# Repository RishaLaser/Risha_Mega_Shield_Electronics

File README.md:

Risha_Mega_Shield_Electronics
=============================

Eagle Schematic and Board Files

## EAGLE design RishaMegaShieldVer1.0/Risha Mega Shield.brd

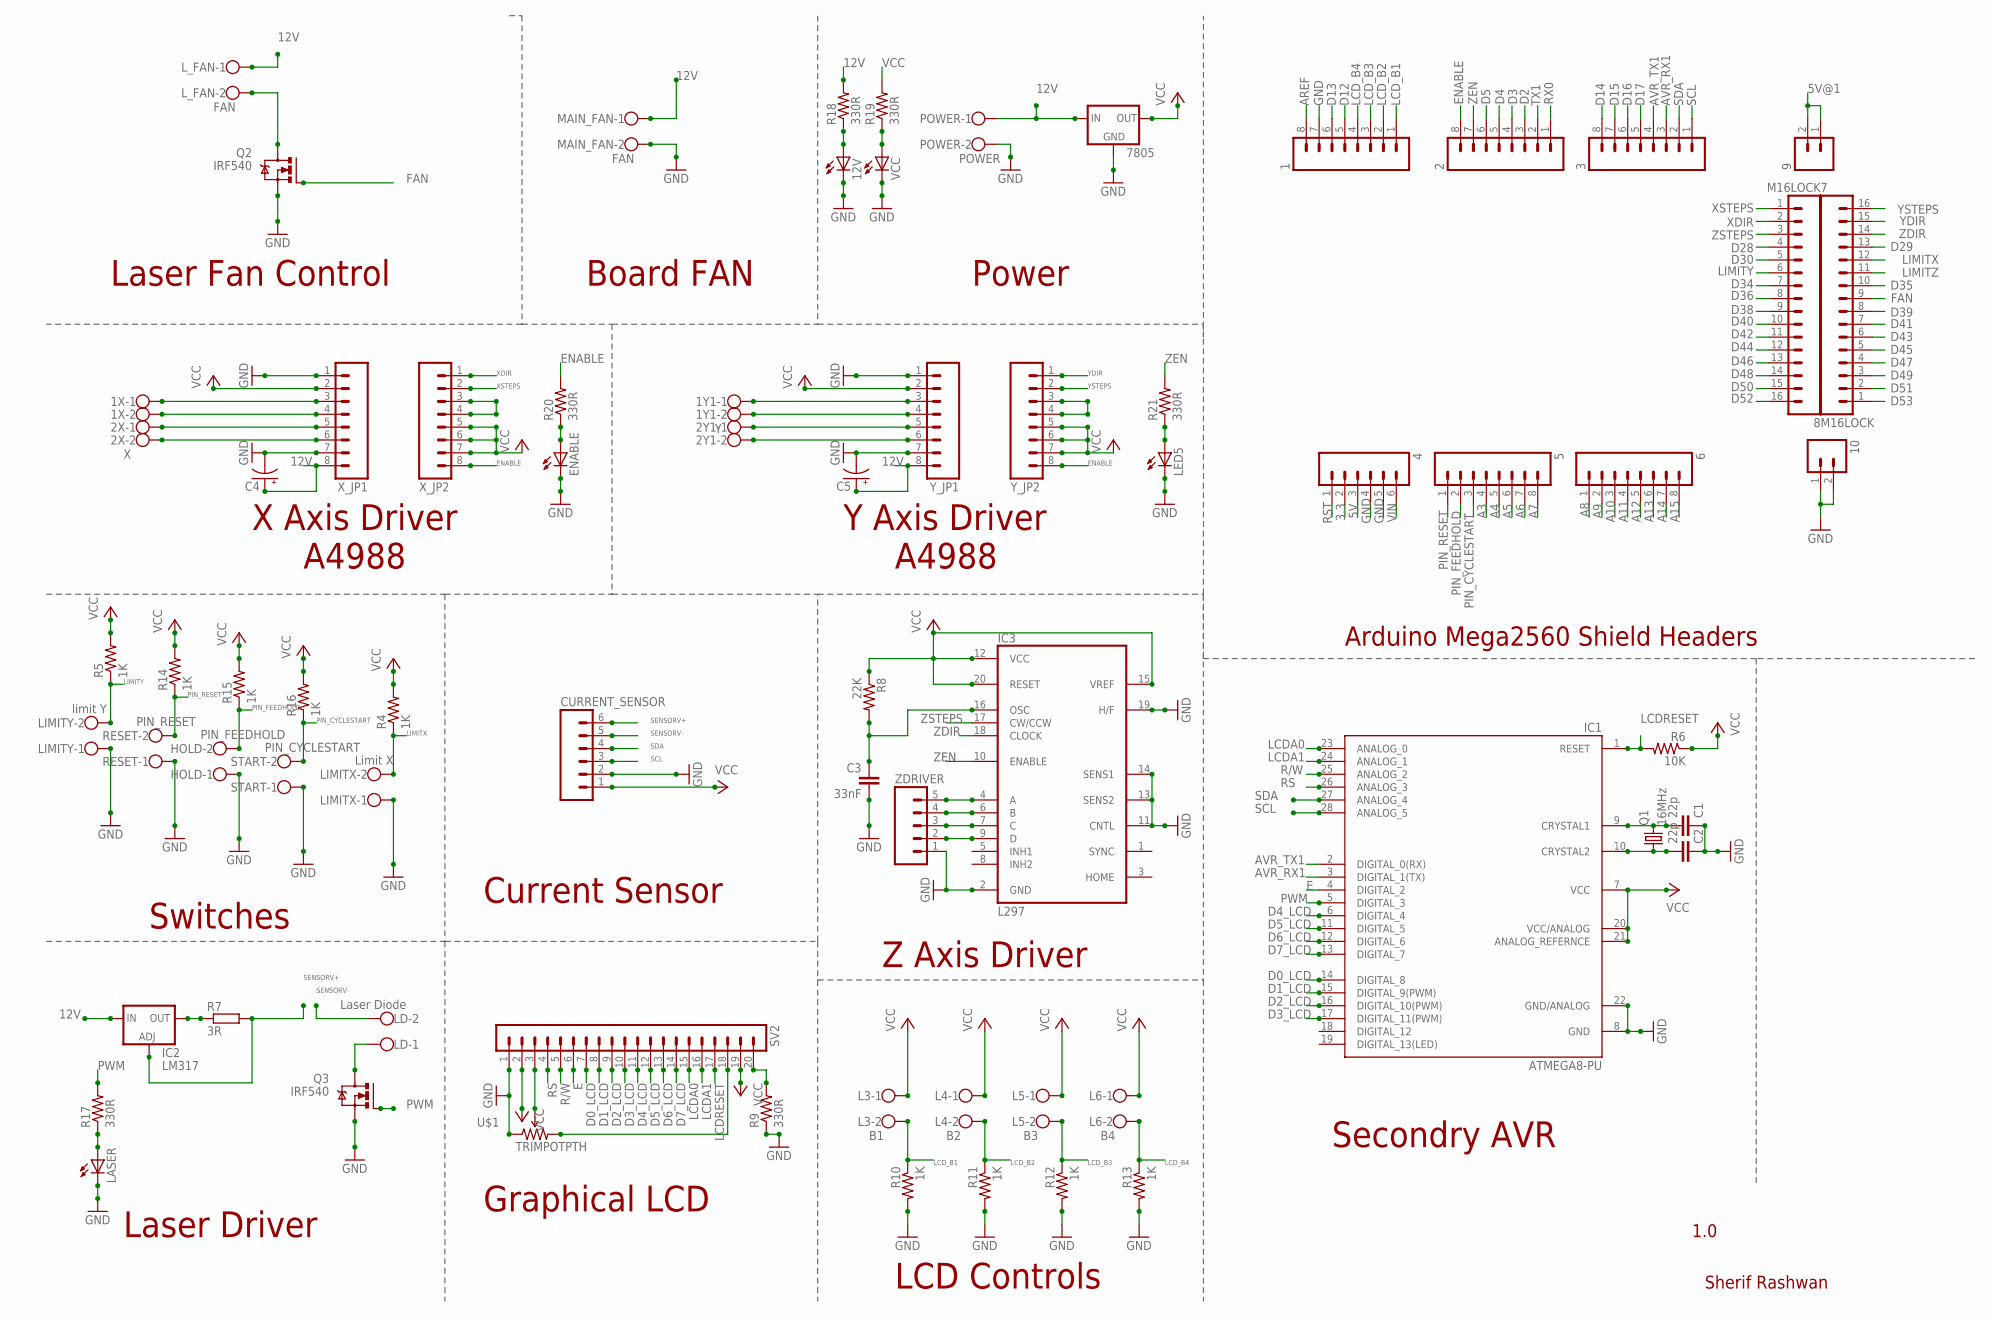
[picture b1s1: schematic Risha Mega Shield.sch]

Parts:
1, 2, 3, 5, 6: M08LOCK; 1X08_LOCK
1X, 2Y1: W237-102
1Y1: Y; W237-102
2X: X; W237-102
4: M06LOCK; 1X06_LOCK
7, 8: M16LOCK; 1X16_LOCK
9, 10: M02LOCK; 1X02_LOCK
12V: LED3MM
7805: V_REG_78XXSINK; TO220-IGO
C1, C2: 22p; C2.5-2
C3: 33nF; C2.5-2
C4, C5: CAP_POLPTH2; CPOL-RADIAL-10UF-25V
CURRENT_SENSOR: M06LONGPADS; 1X06_LONGPADS
ENABLE: LED3MM
HOLD: PIN_FEEDHOLD; W237-102
IC1: ATMEGA8-PU; DIL28-3
IC2: LM317; TO3-K02
IC3: L297; DIL20
L3: B1; W237-102
L4: B2; W237-102
L5: B3; W237-102
L6: B4; W237-102
LASER: LED3MM
LD: Laser Diode; W237-102
LED5: LED3MM
LIMITX: Limit X; W237-102
LIMITY: limit Y; W237-102
L_FAN: FAN; W237-102
MAIN_FAN: FAN; W237-102
POWER: POWER; W237-102
Q1: 16MHz; HC49US
Q2, Q3: IRF540; TO220BV
R4, R5, R10, R11, R12, R13, R14, R15, R16: 1K; 1/6W-RES
R6: 10K; 1/6W-RES
R7: 3R; 0309/12
R8: 22K; 1/6W-RES
R9, R17, R18, R19, R20, R21: 330R; 1/6W-RES
RESET: PIN_RESET; W237-102
START: PIN_CYCLESTART; W237-102
SV2: MA20-1W
U$1: TRIMPOTPTH; TRIM_POT_PTH
VCC: LED3MM
X_JP1, X_JP2: M08; 1X08
Y_JP1, Y_JP2: M08; 1X08
ZDRIVER: M05PTH_LONGPADS; 1X05_LONGPADS

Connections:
3.3: 4.2
5V: 4.3
5V@1: 9.1, 9.2
12V: 7805.IN, C4.1 (+), C5.1 (+), IC2.1 (IN), L_FAN.1, MAIN_FAN.1, POWER.1, R18.2, X_JP1.8, Y_JP1.8
A3: 5.4
A4: 5.5
A5: 5.6
A6: 5.7
A7: 5.8
A8: 6.1
A9: 6.2
A10: 6.3
A11: 6.4
A12: 6.5
A13: 6.6
A14: 6.7
A15: 6.8
AREF: 1.8
AVR_RX1: 3.3, IC1.3 (DIGITAL_1(TX))
AVR_TX1: 3.4, IC1.2 (DIGITAL_0(RX))
D0_LCD: IC1.14 (DIGITAL_8), SV2.7
D1_LCD: IC1.15 (DIGITAL_9(PWM)), SV2.8
D2: 2.3
D2_LCD: IC1.16 (DIGITAL_10(PWM)), SV2.9
D3: 2.4
D3_LCD: IC1.17 (DIGITAL_11(PWM)), SV2.10
D4: 2.5
D4_LCD: IC1.6 (DIGITAL_4), SV2.11
D5: 2.6
D5_LCD: IC1.11 (DIGITAL_5), SV2.12
D6_LCD: IC1.12 (DIGITAL_6), SV2.13
D7_LCD: IC1.13 (DIGITAL_7), SV2.14
D12: 1.5
D13: 1.6
D14: 3.8
D15: 3.7
D16: 3.6
D17: 3.5
D28: 8.4
D29: 7.13
D30: 8.5
D34: 8.7
D35: 7.10
D36: 8.8
D38: 8.9
D39: 7.8
D40: 8.10
D41: 7.7
D42: 8.11
D43: 7.6
D44: 8.12
D45: 7.5
D46: 8.13
D47: 7.4
D48: 8.14
D49: 7.3
D50: 8.15
D51: 7.2
D52: 8.16
D53: 7.1
E: IC1.4 (DIGITAL_2), SV2.6
ENABLE: 2.8, R20.2, X_JP2.8, Y_JP2.8
FAN: 7.9, Q2.G
GND: 1.7, 4.4, 4.5, 10.1, 10.2, 12V.K (C), 7805.GND, C1.1, C2.1, C3.2, C4.2 (-), C5.2 (-), CURRENT_SENSOR.2, ENABLE.K (C), HOLD.1, IC1.8 (GND), IC1.22 (GND/ANALOG), IC3.2 (GND), IC3.11 (CNTL), IC3.13 (SENS2), IC3.14 (SENS1), IC3.19 (H/F), LASER.K (C), LED5.K (C), LIMITX.1, LIMITY.1, MAIN_FAN.2, POWER.2, Q2.S, Q3.S, R9.1, R10.2, R11.2, R12.2, R13.2, RESET.1, START.1, SV2.1, U$1.1 (CCW), VCC.K (C), X_JP1.1, X_JP1.7, Y_JP1.1, Y_JP1.7, ZDRIVER.1
LCDA0: IC1.23 (ANALOG_0), SV2.15
LCDA1: IC1.24 (ANALOG_1), SV2.16
LCDRESET: IC1.1 (RESET), R6.2, SV2.17
LCD_B1: 1.1, L3.2, R10.1
LCD_B2: 1.2, L4.2, R11.1
LCD_B3: 1.3, L5.2, R12.1
LCD_B4: 1.4, L6.2, R13.1
LIMITX: 7.12, LIMITX.2, R4.1
LIMITY: 8.6, LIMITY.2, R5.1
LIMITZ: 7.11
unnamed: L_FAN.2, Q2.D
unnamed: 1Y1.1, Y_JP1.3
unnamed: 1Y1.2, Y_JP1.4
unnamed: 2Y1.1, Y_JP1.5
unnamed: 2Y1.2, Y_JP1.6
unnamed: Y_JP2.3, Y_JP2.4
unnamed: C1.2, IC1.9 (CRYSTAL1), Q1.2
unnamed: C2.2, IC1.10 (CRYSTAL2), Q1.1
unnamed: LASER.A, R17.1
unnamed: IC2.3 (OUT), R7.1
unnamed: LD.1, Q3.D
unnamed: IC3.4 (A), ZDRIVER.5
unnamed: C3.1, IC3.16 (OSC), R8.2
unnamed: IC3.6 (B), ZDRIVER.4
unnamed: IC3.7 (C), ZDRIVER.3
unnamed: IC3.9 (D), ZDRIVER.2
unnamed: SV2.3, U$1.2 (WIPER)
unnamed: 12V.A, R18.1
unnamed: SV2.18, U$1.3 (CW)
unnamed: R19.1, VCC.A
unnamed: ENABLE.A, R20.1
unnamed: LED5.A, R21.1
unnamed: 1X.1, X_JP1.3
unnamed: 1X.2, X_JP1.4
unnamed: 2X.1, X_JP1.5
unnamed: 2X.2, X_JP1.6
unnamed: X_JP2.3, X_JP2.4
unnamed: R9.2, SV2.20
PIN_CYCLESTART: 5.3, R16.1, START.2
PIN_FEEDHOLD: 5.2, HOLD.2, R15.1
PIN_RESET: 5.1, R14.1, RESET.2
PWM: IC1.5 (DIGITAL_3), Q3.G, R17.2
R/W: IC1.25 (ANALOG_2), SV2.5
RS: IC1.26 (ANALOG_3), SV2.4
RST: 4.1
RX0: 2.1
SCL: 3.1, CURRENT_SENSOR.3, IC1.28 (ANALOG_5)
SDA: 3.2, CURRENT_SENSOR.4, IC1.27 (ANALOG_4)
SENSORV+: CURRENT_SENSOR.6, IC2.2 (ADJ), R7.2
SENSORV-: CURRENT_SENSOR.5, LD.2
TX1: 2.2
VCC: 7805.OUT, CURRENT_SENSOR.1, IC1.7 (VCC), IC1.20 (VCC/ANALOG), IC1.21 (ANALOG_REFERNCE), IC3.12 (VCC), IC3.15 (VREF), IC3.20 (RESET), L3.1, L4.1, L5.1, L6.1, R4.2, R5.2, R6.1, R8.1, R14.2, R15.2, R16.2, R19.2, SV2.2, SV2.19, X_JP1.2, X_JP2.5, X_JP2.6, X_JP2.7, Y_JP1.2, Y_JP2.5, Y_JP2.6, Y_JP2.7
VIN: 4.6
XDIR: 8.2, X_JP2.1
XSTEPS: 8.1, X_JP2.2
YDIR: 7.15, Y_JP2.1
YSTEPS: 7.16, Y_JP2.2
ZDIR: 7.14, IC3.18 (CLOCK)
ZEN: 2.7, IC3.10 (ENABLE), R21.2
ZSTEPS: 8.3, IC3.17 (CW/CCW)

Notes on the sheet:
Arduino Mega2560 Shield Headers
1.0
Sherif Rashwan
X Axis Driver
A4988
Current Sensor
Power
Laser Fan Control
Board FAN
Switches
Y Axis Driver
Secondry AVR
Laser Driver
Z Axis Driver
Graphical LCD
LCD Controls

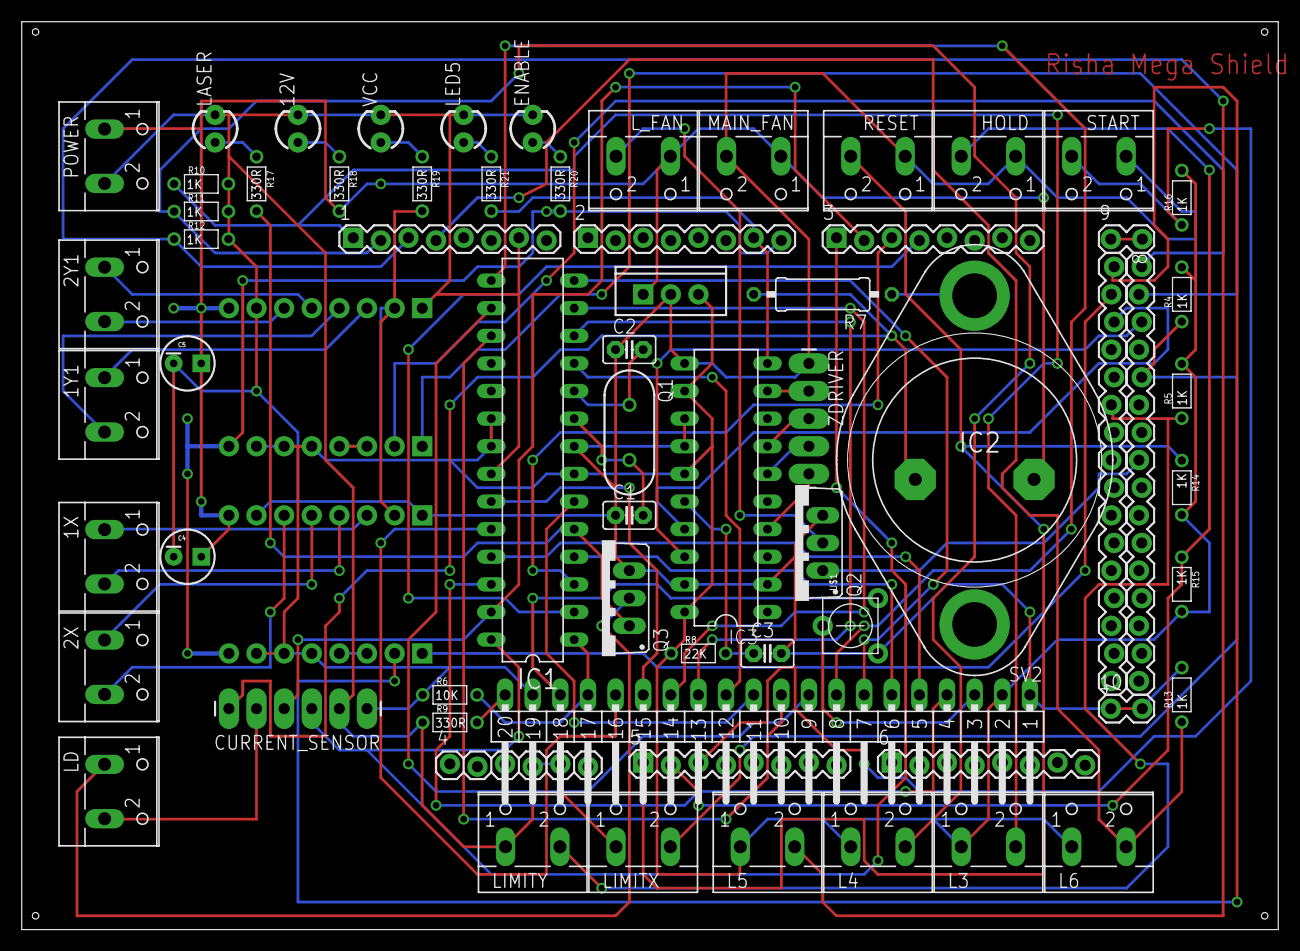
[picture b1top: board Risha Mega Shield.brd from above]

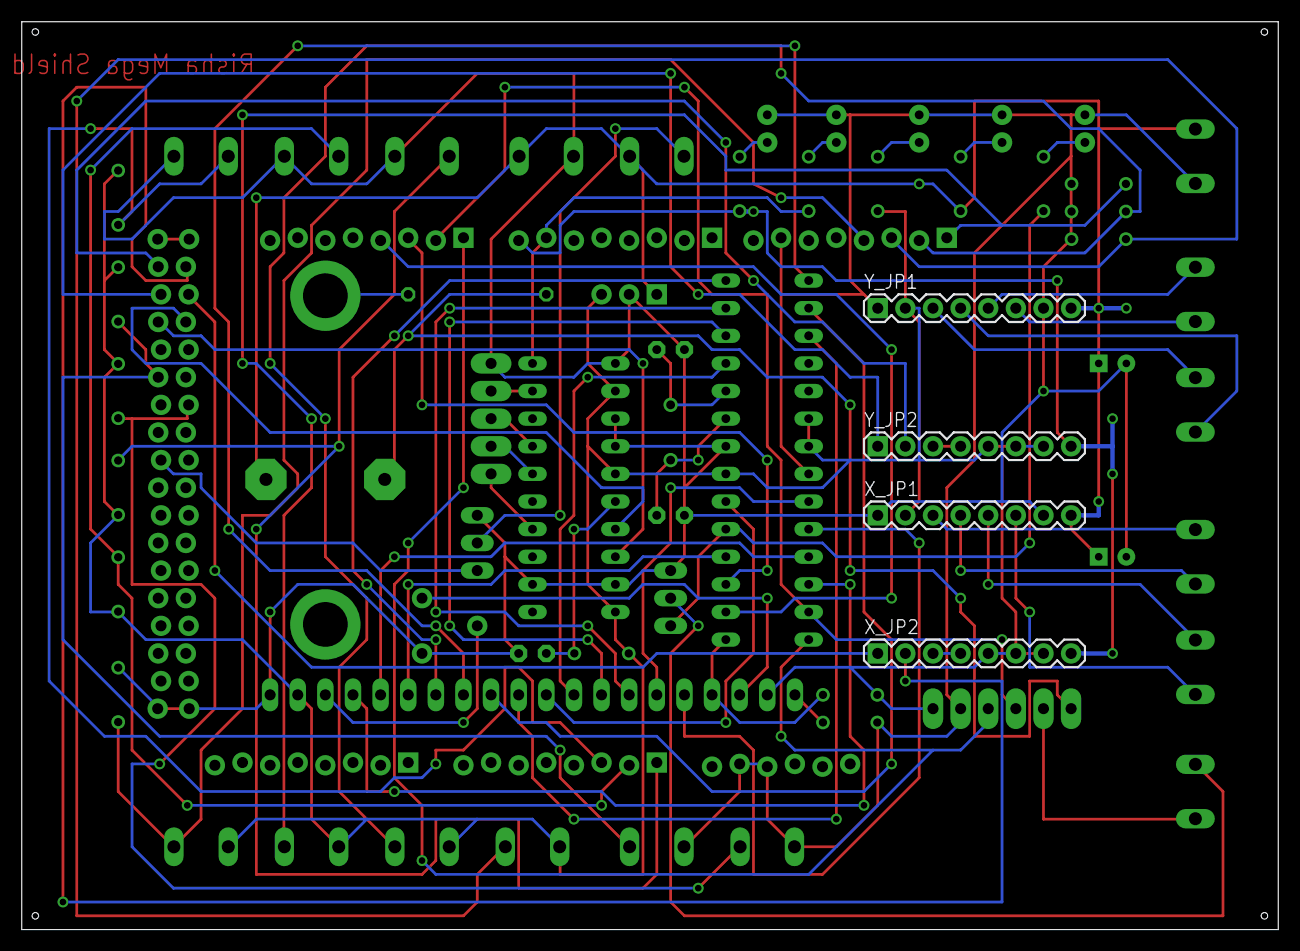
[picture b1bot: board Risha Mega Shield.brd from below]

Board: 2 copper layers, 115.5 x 83.5 mm, 70 parts (4 on the bottom side), 71 nets.
